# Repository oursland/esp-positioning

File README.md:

# Positioning via IMU-aided WiFi FTM and UWB on an ESP32-S3

## Overview

There is ample research into the accuracy of Ulra Wideband (UWB)-based ranging and positioning, WiFi Fine Timing Measurements (WiFi FTM)-based ranging and positioning, and an Inertial Measurement Unit (IMU) augmentation of such systems.  Most of the work was performed with purpose-designed systems or smartphones, but very little was performed using Espressif SoCs including the ESP32-S3.

Based on the findings of previous works, it's expected that WiFi FTM may be only valuable for positioning information to about 1 meter accuracy while UWB sensors can provide measurements accurate down to around 10 centimeters.  UWB has limited range, particularly in indoor and cluttered environments where the signals fail to penetrate through walls or other obstacles.  This suggests that if accuracy is a requirement, it may be required to install a UWB transciever but also utilize WiFi FTM to provide rough positioning should the UWB signal be lost.

Sensor fusion and state estimation through Kalman filtering can provide better positioning estimates over naive approaches using WiFi FTM, UWB, or IMU measurements alone.  Previous research have been performed using Extended Kalman Filtering (EKF) and Unscented Kalman Filter (UKF) approaches, but publications for Invariant Extended Kalman Filter (InEKF) have not been identified.

### Questions

1. Given the utility for low-cost, low-power, and reduced bill-of-materials positioning for small, low-cost robots, can we use the ESP32-S3's WiFi Fine Timing Measurements (WiFi FTM) in 802.11mc standard and an IMU for positioning without additional sensors?

2. Will the inclusion of a UWB sensor bring sufficient value to offset their additional cost, complexity, and power consumption?

3. Can the redundancy in Time Difference of Arrival (TDOA) measurements from WiFi FTM and UWB be used to improve accuracy beyond either WiFi FTM or UWB alone?

## Objective

This experiment is to compare and contrast position estimation of systems:

    1. IMU and WiFi FTM
    2. IMU and UWB
    3. IMU with WiFi FTM and UWB

## Experiment Design

To perform this experiment, a custom design was created using:

* Espressif ESP32-S3-WROOM-2 module
* STMicroelectronics ISM330DHCX IMU
* Qorvo DWM1000 UWB module
* 2 AAA battery holder

Circuit Diagram and PCB Layout can be found in the [`kicad/`](kicad/) directory.

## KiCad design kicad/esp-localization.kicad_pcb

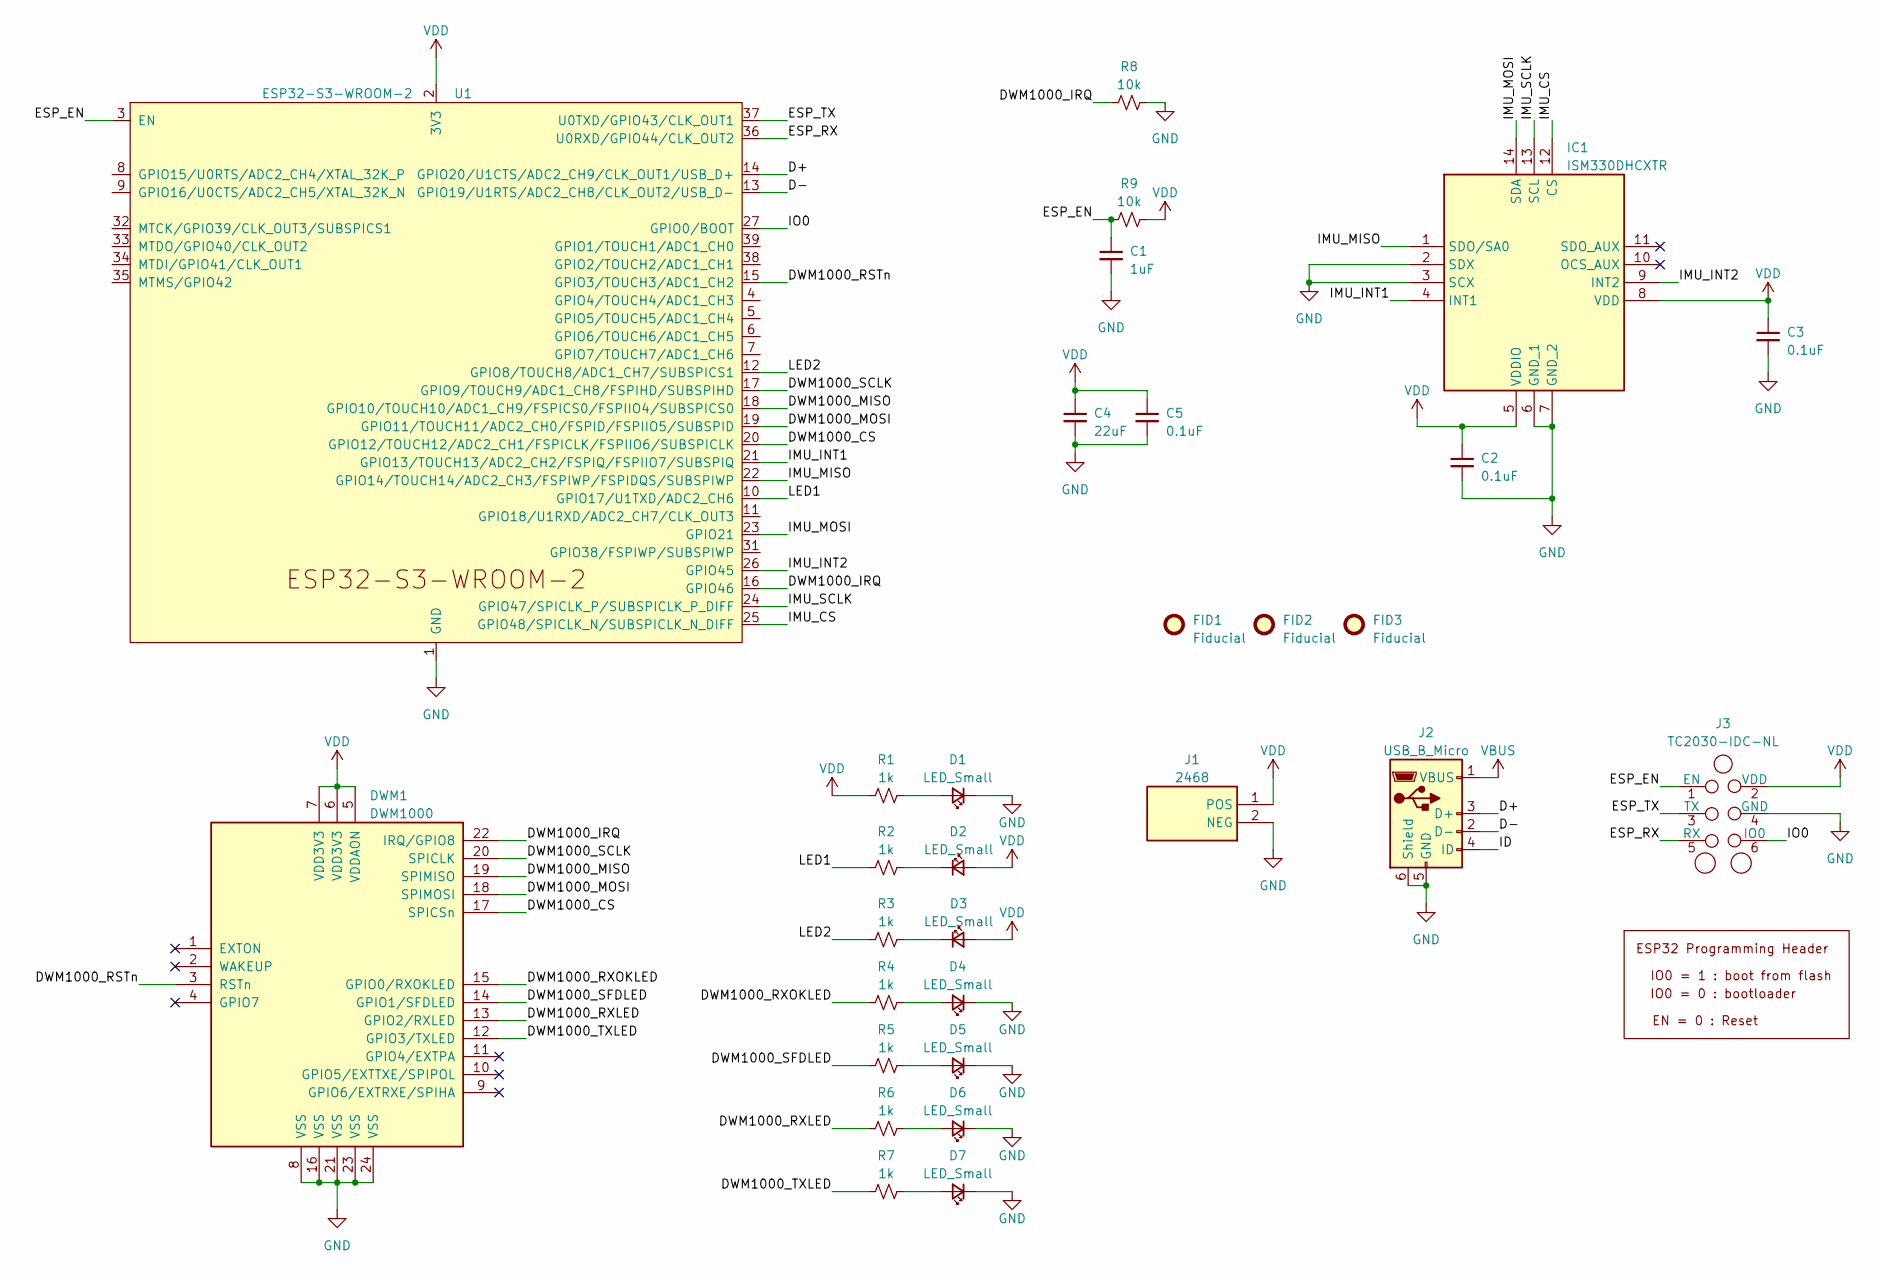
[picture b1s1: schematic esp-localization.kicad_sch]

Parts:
C1: 1uF; C_0805_2012Metric
C2, C3, C5: 0.1uF; C_0603_1608Metric
C4: 22uF; C_0805_2012Metric
D1, D2, D3, D4, D5, D6, D7: LED_Small; LED_0603_1608Metric
DWM1: DWM1000
FID1, FID2, FID3: Fiducial; Fiducial_0.5mm_Mask1mm
IC1: ISM330DHCXTR; LGA-14_2.5X3X0.86_; Mouser Part Number 511-ISM330DHCXTR
J1: 2468; Mouser Part Number 534-2468
J2: USB_B_Micro; USB_Micro-B_Amphenol_10104110_Horizontal
J3: TC2030-IDC-NL_ESP; Tag-Connect_TC2030-IDC-NL_2x03_P1.27mm_Vertical
R1, R2, R3, R4, R5, R6, R7: 1k; R_0603_1608Metric
R8, R9: 10k; R_0603_1608Metric
U1: ESP32-S3-WROOM-2

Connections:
/D+: J2.3 (D+), U1.14 (GPIO20/U1CTS/ADC2_CH9/CLK_OUT1/USB_D+)
/D-: J2.2 (D-), U1.13 (GPIO19/U1RTS/ADC2_CH8/CLK_OUT2/USB_D-)
/DWM1000_CS: DWM1.17 (SPICSn), U1.20 (GPIO12/TOUCH12/ADC2_CH1/FSPICLK/FSPIIO6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)
/DWM1000_IRQ: DWM1.22 (IRQ/GPIO8), R8.1, U1.16 (GPIO46)
/DWM1000_MISO: DWM1.19 (SPIMISO), U1.18 (GPIO10/TOUCH10/ADC1_CH9/FSPICS0/FSPIIO4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)
/DWM1000_MOSI: DWM1.18 (SPIMOSI), U1.19 (GPIO11/TOUCH11/ADC2_CH0/FSPID/FSPIIO5/S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)
/DWM1000_RSTn: DWM1.3 (RSTn), U1.15 (GPIO3/TOUCH3/ADC1_CH2)
/DWM1000_RXLED: DWM1.13 (GPIO2/RXLED), R6.1
/DWM1000_RXOKLED: DWM1.15 (GPIO0/RXOKLED), R4.1
/DWM1000_SCLK: DWM1.20 (SPICLK), U1.17 (GPIO9/TOUCH9/ADC1_CH8/FSPIHD/SUBSPIHD)
/DWM1000_SFDLED: DWM1.14 (GPIO1/SFDLED), R5.1
/DWM1000_TXLED: DWM1.12 (GPIO3/TXLED), R7.1
/ESP_EN: C1.1, J3.1 (EN), R9.1, U1.3 (EN)
/ESP_RX: J3.5 (RX), U1.36 (U0RXD/GPIO44/CLK_OUT2)
/ESP_TX: J3.3 (TX), U1.37 (U0TXD/GPIO43/CLK_OUT1)
/ID: J2.4 (ID)
/IMU_CS: IC1.12 (CS), U1.25 (GPIO48/SPICLK_N/SUBSPICLK_N_DIFF)
/IMU_INT1: IC1.4 (INT1), U1.21 (GPIO13/TOUCH13/ADC2_CH2/FSPIQ/FSPIIO7/S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)
/IMU_INT2: IC1.9 (INT2), U1.26 (GPIO45)
/IMU_MISO: IC1.1 (SDO/SA0), U1.22 (GPIO14/TOUCH14/ADC2_CH3/FSPIWP/FSPIDQS/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)
/IMU_MOSI: IC1.14 (SDA), U1.23 (GPIO21)
/IMU_SCLK: IC1.13 (SCL), U1.24 (GPIO47/SPICLK_P/SUBSPICLK_P_DIFF)
/IO0: J3.6 (IO0), U1.27 (GPIO0/BOOT)
/LED1: R2.1, U1.10 (GPIO17/U1TXD/ADC2_CH6)
/LED2: R3.1, U1.12 (GPIO8/TOUCH8/ADC1_CH7/SUBSPICS1)
GND: C1.2, C2.2, C3.2, C4.2, C5.2, D1.1 (K), D4.1 (K), D5.1 (K), D6.1 (K), D7.1 (K), DWM1.8 (VSS), DWM1.16 (VSS), DWM1.21 (VSS), DWM1.23 (VSS), DWM1.24 (VSS), IC1.2 (SDX), IC1.3 (SCX), IC1.6 (GND_1), IC1.7 (GND_2), J1.2 (NEG), J2.5 (GND), J2.6 (Shield), J3.4 (GND), R8.2, U1.1 (GND), U1.40 (GND), U1.41 (GND)
unnamed: D1.2 (A), R1.2
unnamed: D2.1 (K), R2.2
unnamed: D3.1 (K), R3.2
unnamed: D4.2 (A), R4.2
unnamed: D5.2 (A), R5.2
unnamed: D6.2 (A), R6.2
unnamed: D7.2 (A), R7.2
VBUS: J2.1 (VBUS)
VDD: C2.1, C3.1, C4.1, C5.1, D2.2 (A), D3.2 (A), DWM1.5 (VDDAON), DWM1.6 (VDD3V3), DWM1.7 (VDD3V3), IC1.5 (VDDIO), IC1.8 (VDD), J1.1 (POS), J3.2 (VDD), R1.1, R9.2, U1.2 (3V3)

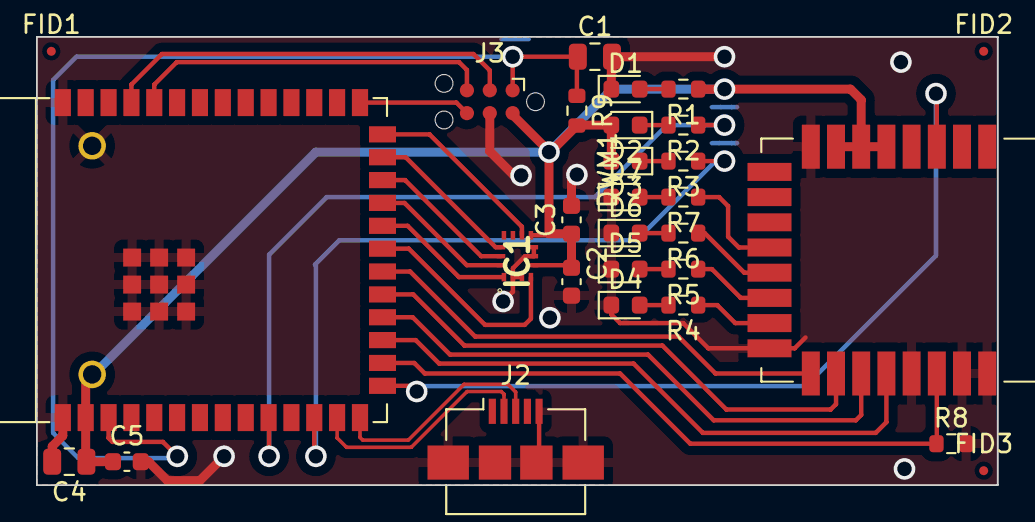
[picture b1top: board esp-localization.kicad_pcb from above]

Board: 2 copper layers, 53.4 x 24.9 mm, 30 parts (1 on the bottom side), 33 nets.

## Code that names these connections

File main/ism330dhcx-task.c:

#include "ism330dhcx-task.h"

#include <stdio.h>
#include <stdlib.h>
#include <string.h>
#include <inttypes.h>

#include "freertos/FreeRTOS.h"
#include "freertos/queue.h"
#include "freertos/task.h"

#include "esp_chip_info.h"
#include "esp_flash.h"
#include "esp_log.h"
#include "esp_timer.h"

#include "driver/gpio.h"
#include "driver/spi_master.h"
#include "rom/ets_sys.h"

#include "ism330dhcx_reg.h"

#define TAG         "ism330dhcx-task"

#define IMU_HOST    SPI2_HOST
#define IMU_CS      GPIO_NUM_48
#define IMU_SCLK    GPIO_NUM_47
#define IMU_MISO    GPIO_NUM_14
#define IMU_MOSI    GPIO_NUM_21
#define IMU_INT1    GPIO_NUM_13
#define IMU_INT2    GPIO_NUM_45

static int32_t stmdev_write(void *handle, uint8_t reg, const uint8_t *data, uint16_t len) {
    spi_device_handle_t spi = (spi_device_handle_t)handle;
    spi_transaction_t t = {
        .addr = reg,
        .length = len*8,
        .tx_buffer = (const void *)data,
    };
    esp_err_t err = spi_device_polling_transmit(spi, &t);
    if(err != ESP_OK) {
        return -1;
    }
    return 0;
}

static int32_t stmdev_read(void *handle, uint8_t reg, uint8_t *data, uint16_t len) {
    spi_device_handle_t spi = (spi_device_handle_t)handle;
    spi_transaction_t t = {
        .addr = reg | 0x80,
        .length = len*8,
        .rxlength = len*8,
        .rx_buffer = (void *)data,
    };
    esp_err_t err = spi_device_polling_transmit(spi, &t);
    if(err != ESP_OK) {
        return -1;
    }
    return 0;
}

static void stmdev_mdelay(uint32_t millisec) {
    vTaskDelay(pdMS_TO_TICKS(millisec));
}

void ism330dhcx_task_func(void *args) {
    ESP_LOGI(TAG, "Starting ISM330DHCX Task");

    // ISM330DHCX
    esp_err_t ret;
    spi_device_handle_t imu_spi_handle;
    spi_bus_config_t imu_bus_config = {
        .mosi_io_num = IMU_MOSI,
        .miso_io_num = IMU_MISO,
        .sclk_io_num = IMU_SCLK,
        .quadwp_io_num = -1,
    };
    spi_device_interface_config_t imu_device_config = {
        .address_bits = 8,
        .clock_speed_hz = SPI_MASTER_FREQ_10M,
        .spics_io_num = IMU_CS,
        .queue_size = 1,
    };
    ret = spi_bus_initialize(IMU_HOST, &imu_bus_config, SPI_DMA_CH_AUTO);
    ESP_ERROR_CHECK(ret);
    ret=spi_bus_add_device(IMU_HOST, &imu_device_config, &imu_spi_handle);
    ESP_ERROR_CHECK(ret);

    vTaskDelay(pdMS_TO_TICKS(10));

    stmdev_ctx_t dev_ctx;
    dev_ctx.read_reg = stmdev_read;
    dev_ctx.write_reg = stmdev_write;
    dev_ctx.handle = imu_spi_handle;

    uint8_t whoamI;
    ism330dhcx_device_id_get(&dev_ctx, &whoamI);
    ESP_LOGI(TAG, "Received ID %02X, expected %02X", whoamI, ISM330DHCX_ID);

    ism330dhcx_reset_set(&dev_ctx, PROPERTY_ENABLE);

    uint8_t rst;
    do {
        ism330dhcx_reset_get(&dev_ctx, &rst);
    } while (rst);

    /* Start device configuration. */
    ism330dhcx_device_conf_set(&dev_ctx, PROPERTY_ENABLE);
    /* Enable Block Data Update */
    ism330dhcx_block_data_update_set(&dev_ctx, PROPERTY_ENABLE);
    /* Accelerometer Self Test */
    /* Set Output Data Rate */
    ism330dhcx_xl_data_rate_set(&dev_ctx, ISM330DHCX_XL_ODR_52Hz);
    /* Set full scale */
    ism330dhcx_xl_full_scale_set(&dev_ctx, ISM330DHCX_4g);

    while(true) {
        int16_t data_raw[3];
        ism330dhcx_acceleration_raw_get(&dev_ctx, data_raw);

        ESP_LOGI(TAG, "[%6d] [%6d] [%6d]", data_raw[0], data_raw[1], data_raw[2]);

        vTaskDelay(pdMS_TO_TICKS(100));
    }
}

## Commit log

2023-04-09 Initial commit.
2023-04-18 Add Hello World sample code.
2023-04-18 Add kicad files.
2023-04-27 Add ISM330DHCX and DW1000 drivers.
2023-04-27 Add DW1000, ISM330DHCX, and FTM tasks.
2023-04-27 Update main to launch tasks.
2023-04-28 Update README.md with some overview of the project.
